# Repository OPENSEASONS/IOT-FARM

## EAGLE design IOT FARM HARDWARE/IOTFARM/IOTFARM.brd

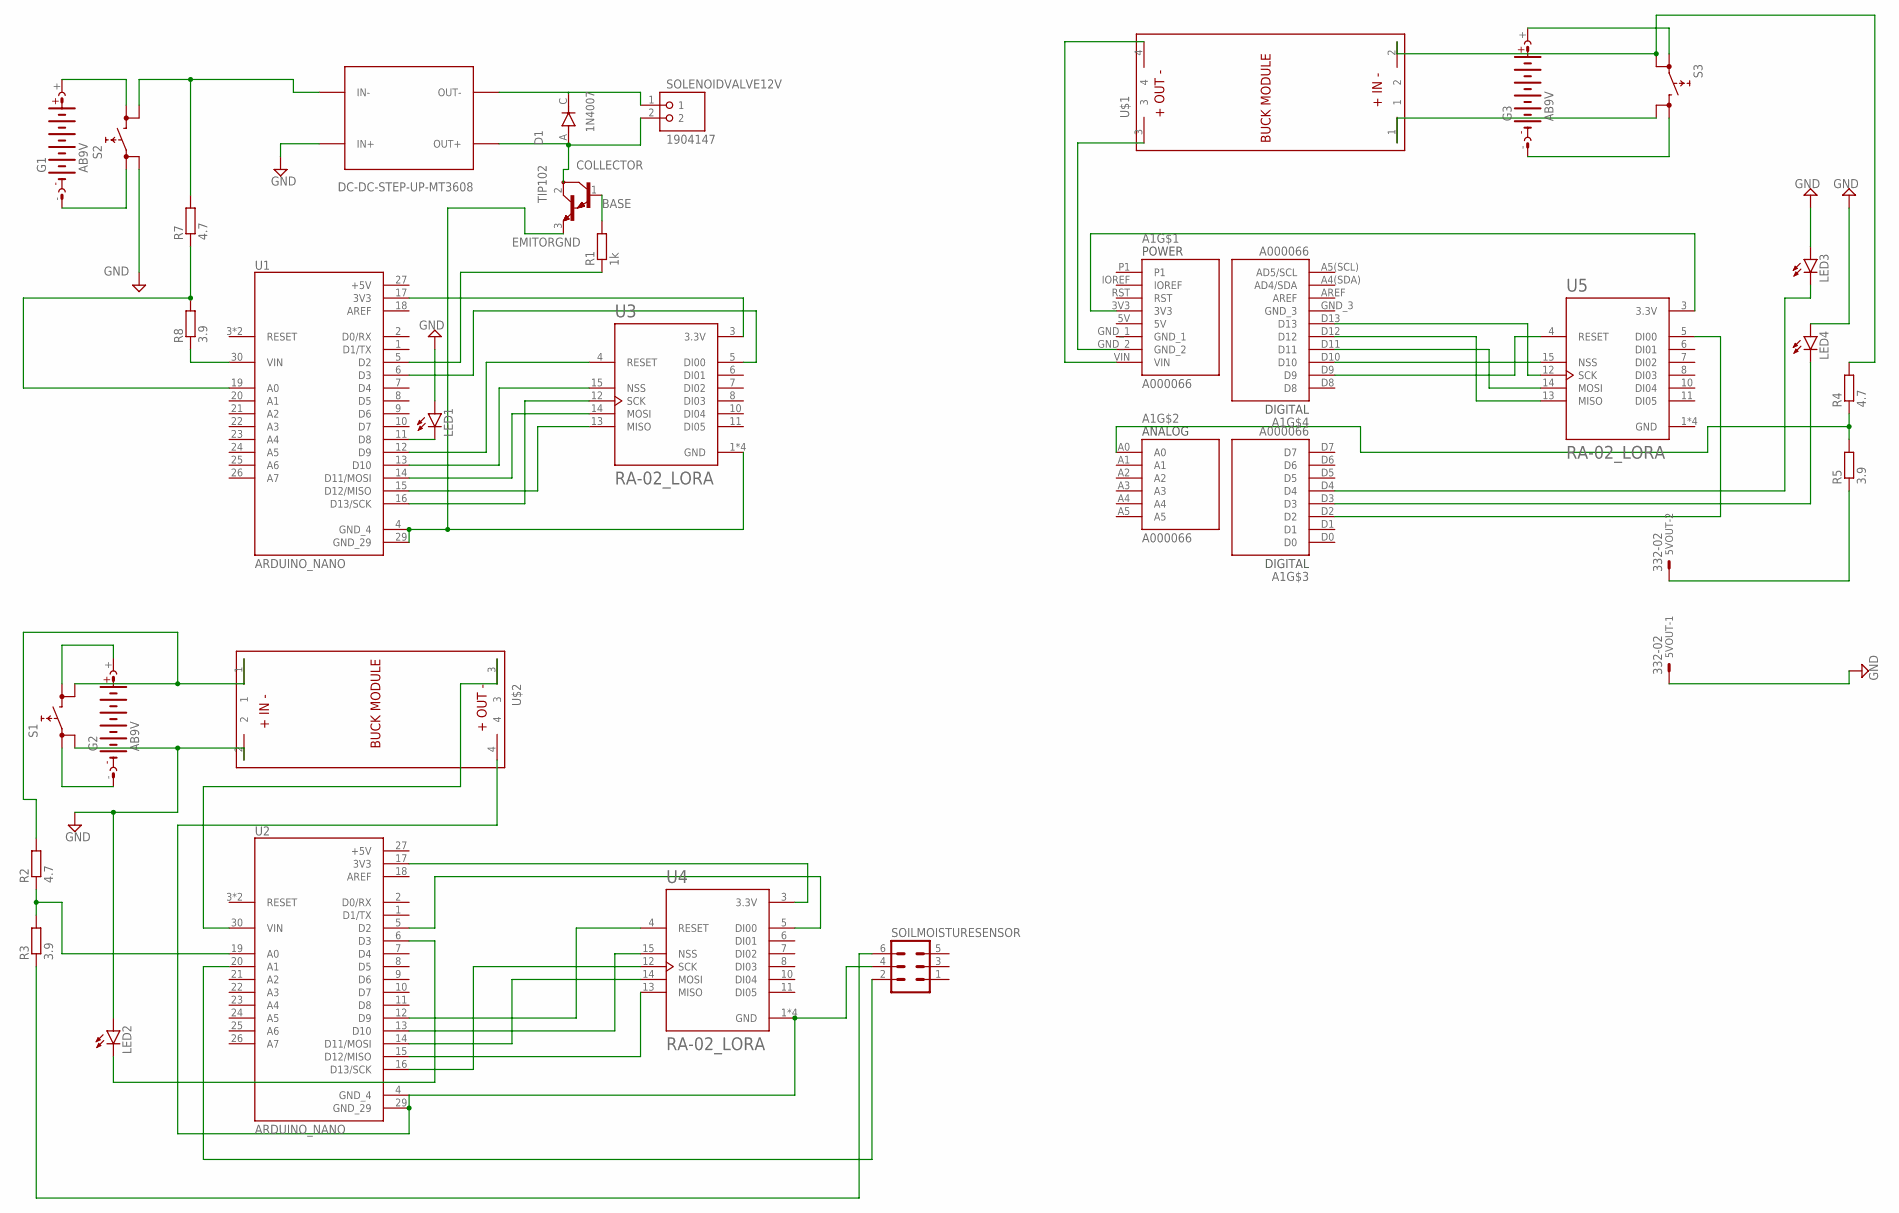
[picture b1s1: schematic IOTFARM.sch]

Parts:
5VOUT: 332-02
A1: A000066; ARDUINO_A000066
D1: 1N4007; DIOAD1060W80L520D270
G1, G2, G3: AB9V
LED1, LED2, LED3, LED4: LED3MM
R1: 1k; 0204V
R2, R4, R7: 4.7; 0204V
R3, R5, R8: 3.9; 0204V
S1, S2, S3: REKN
SOILMOISTURESENSOR: MA03-2
SOLENOIDVALVE12V: 1904147; PHOENIX_1904147
U1, U2: ARDUINO_NANO; MODULE_ARDUINO_NANO
U3, U4, U5: RA-02_LORA; MODULE_RA-02_LORA
U$1, U$2: BUCK_MODULEWITH_SMDPADS&THROUGHHOLES; BUCK_MODULE
U$3: DC-DC-STEP-UP-MT3608
U$4: TIP102; TO220V

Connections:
5V: A1.5V
+5V: U1.27 (+5V), U2.27 (+5V)
AREF: U1.18 (AREF), U2.18 (AREF)
BASE: R1.2, U$4.1 (B)
COLLECTOR: D1.A, SOLENOIDVALVE12V.2, U$3.OUT+, U$4.2 (C)
EMITORGND: U1.4 (GND_4), U1.29 (GND_29), U3.1 (GND), U3.2 (GND), U3.9 (GND), U3.16 (GND), U$4.3 (E)
GND: 5VOUT.1, LED1.A, LED2.A, LED3.A, LED4.A, S1.0B (0), S2.0B (0), U5.1 (GND), U5.2 (GND), U5.9 (GND), U5.16 (GND), U$2.2, U$3.IN+
GND_1: A1.GND_1
GND_3: A1.GND_3
unnamed: R7.2, S2.1B (1), U$3.IN-
unnamed: D1.C, SOLENOIDVALVE12V.1, U$3.OUT-
unnamed: LED1.K (C), U1.11 (D8)
unnamed: G2.+, S1.1A (1)
unnamed: R1.1, U1.5 (D2)
unnamed: U1.12 (D9), U3.4 (RESET)
unnamed: G1.+, S2.1A (1)
unnamed: U1.13 (D10), U3.15 (NSS)
unnamed: U1.6 (D3), U3.5 (DI00)
unnamed: U1.16 (D13/SCK), U3.12 (SCK)
unnamed: U1.15 (D12/MISO), U3.13 (MISO)
unnamed: U1.14 (D11/MOSI), U3.14 (MOSI)
unnamed: U1.17 (3V3), U3.3 (3.3V)
unnamed: R8.1, U1.30 (VIN)
unnamed: R7.1, R8.2, U1.19 (A0)
unnamed: G1.-, S2.0A (0)
unnamed: G2.-, S1.0A (0)
unnamed: R2.2, S1.1B (1), U$2.1
unnamed: R3.1, SOILMOISTURESENSOR.6
unnamed: U2.30 (VIN), U$2.3
unnamed: SOILMOISTURESENSOR.4, U2.4 (GND_4), U2.29 (GND_29), U4.1 (GND), U4.2 (GND), U4.9 (GND), U4.16 (GND), U$2.4
unnamed: U2.17 (3V3), U4.3 (3.3V)
unnamed: U2.12 (D9), U4.4 (RESET)
unnamed: U2.14 (D11/MOSI), U4.14 (MOSI)
unnamed: U2.15 (D12/MISO), U4.13 (MISO)
unnamed: U2.16 (D13/SCK), U4.12 (SCK)
unnamed: U2.13 (D10), U4.15 (NSS)
unnamed: SOILMOISTURESENSOR.2, U2.20 (A1)
unnamed: R2.1, R3.2, U2.19 (A0)
unnamed: U2.5 (D2), U4.5 (DI00)
unnamed: LED2.K (C), U2.6 (D3)
unnamed: G3.+, S3.0A (0)
unnamed: R4.2, S3.0B (0), U$1.2
unnamed: S3.1B (1), U$1.1
unnamed: A1.VIN, U$1.4
unnamed: A1.GND_2, U$1.3
unnamed: A1.D9, U5.4 (RESET)
unnamed: A1.D11, U5.14 (MOSI)
unnamed: A1.D12, U5.13 (MISO)
unnamed: A1.D10, U5.15 (NSS)
unnamed: A1.D13, U5.12 (SCK)
unnamed: A1.3V3, U5.3 (3.3V)
unnamed: A1.D2, U5.5 (DI00)
unnamed: A1.D3, LED4.K (C)
unnamed: A1.D4, LED3.K (C)
unnamed: G3.-, S3.1A (1)
unnamed: A1.A0, R4.1, R5.2
unnamed: 5VOUT.2, R5.1

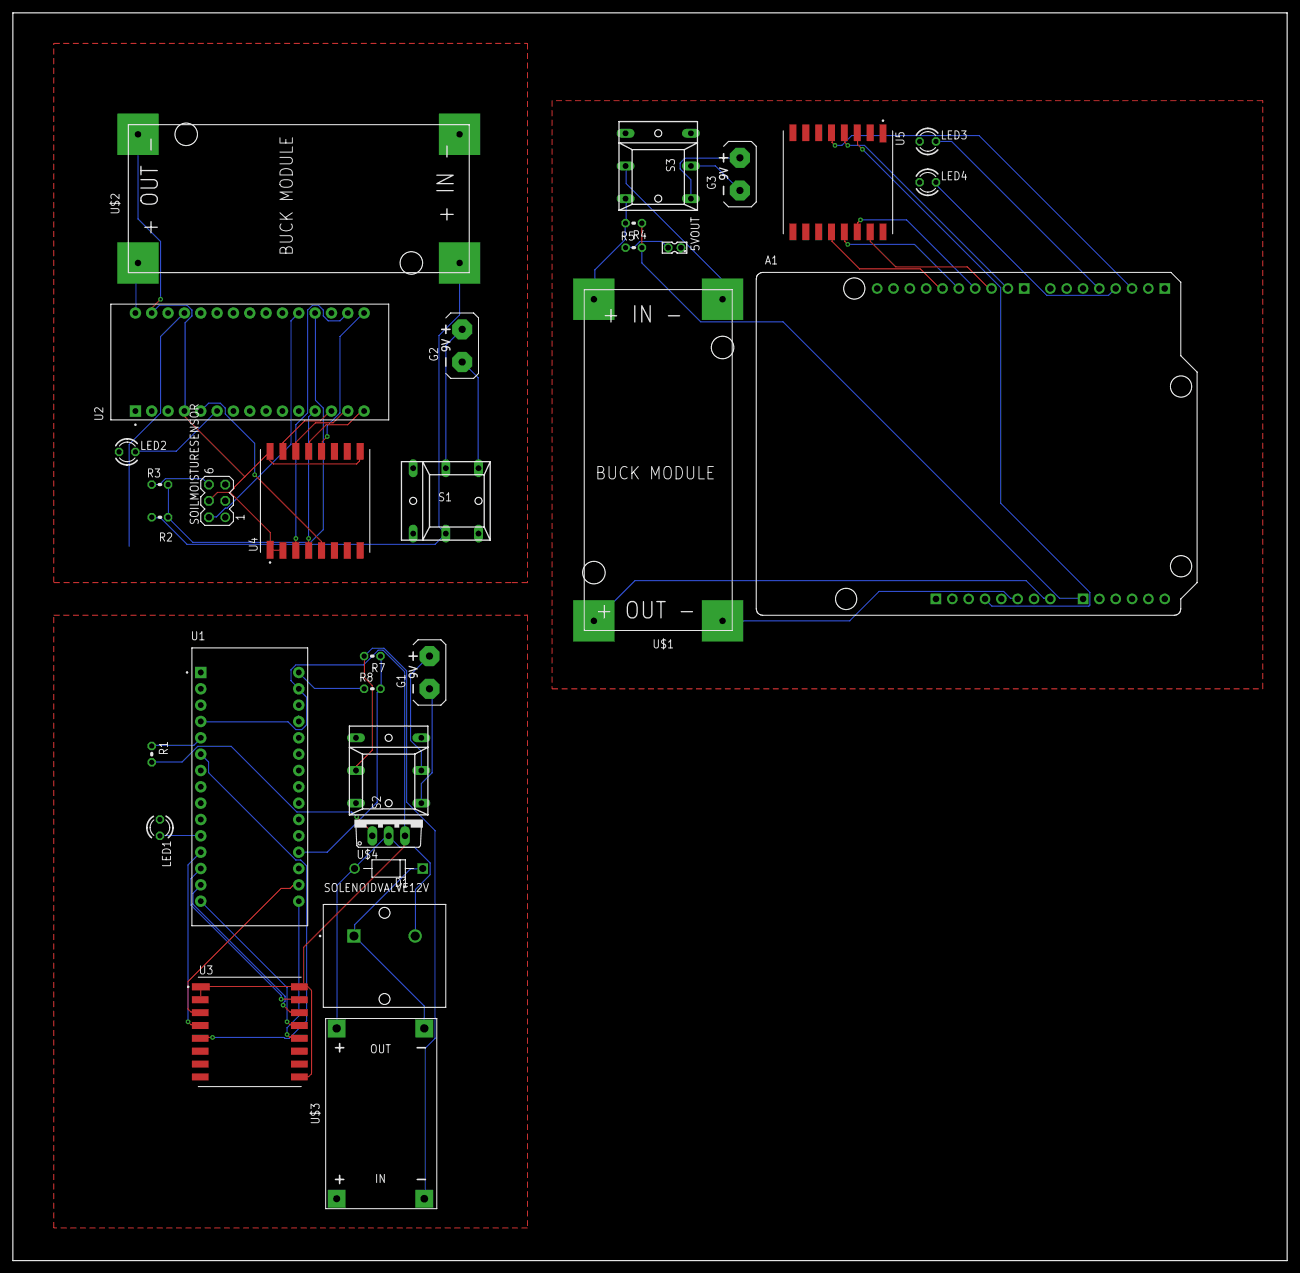
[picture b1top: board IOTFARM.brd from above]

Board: 2 copper layers, 198.1 x 194.0 mm, 31 parts (0 on the bottom side), 54 nets.

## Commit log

2025-10-12 Arduino Build And Make
2025-10-13 MAster Slave P5js visualization
2025-10-19 Added The PCB HARDWARE
2025-10-20 Sketch uses 20166 bytes (62%) of program storage space. Maximum is 32256 bytes.
2025-11-02 Port ESP32 code to ESP8266 and refactor SPI/MQTT
    Replaced ESP32-specific libraries with ESP8266WiFi and adjusted SPI pin definitions for ESP8266 compatibility. Simplified serial output and removed verbose debug messages. Refactored SPI initializati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
2025-11-02 Sketch uses 25504 bytes (79%) of program storage space. Maximum is 32256 bytes. Global variables use 1459 bytes (71%) of dynamic memory, leaving 589 bytes for local variables. Maximum is 2048 bytes.W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
2025-11-02 Add Blink2 LoRa mesh node and minor Esp32 update
    Introduced Blink2.ino for a LoRa mesh node with solenoid control and data bundling. Also added a blank line in Esp32.ino for improved code readability.
2025-11-02 Add LoRa mesh hygrometer node implementation
    Introduces Blink3.ino for a LoRa mesh hygrometer node using Nano and RA-02. Features include reading soil moisture, sending data and routing table to master node, battery voltage monitoring, and mesh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
2025-11-02 Remove MASTER and migrate files to IOT FIMWARE
    Deleted the MASTER and NODE directories, including build scripts, source files, and configuration. Renamed Blink and Esp32 project files from mastertwo to IOT FIMWARE, consolidating firmware sources 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
